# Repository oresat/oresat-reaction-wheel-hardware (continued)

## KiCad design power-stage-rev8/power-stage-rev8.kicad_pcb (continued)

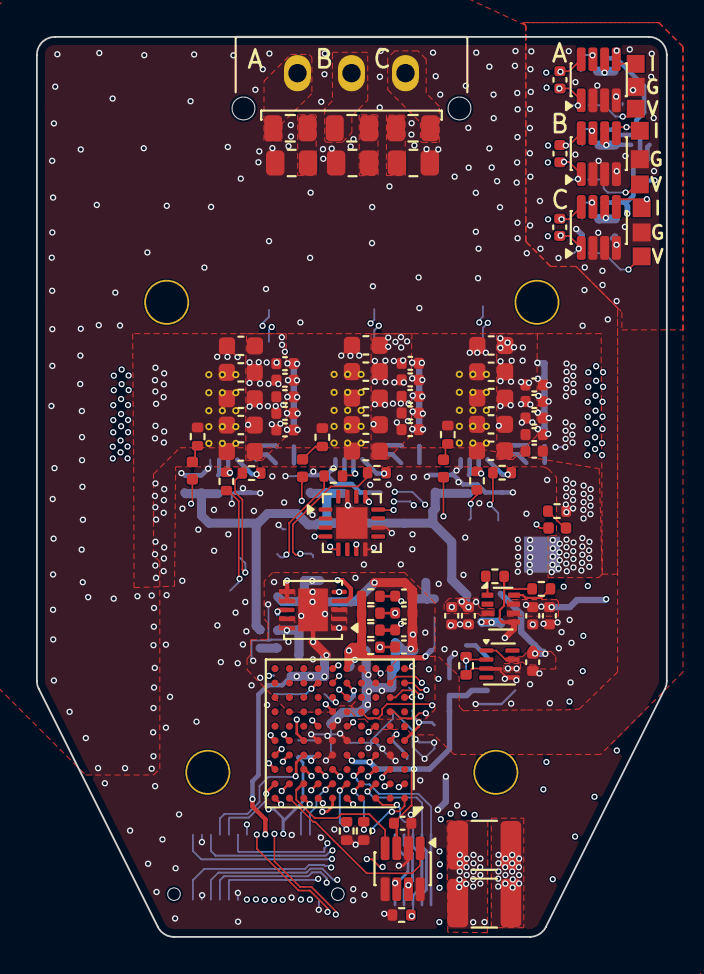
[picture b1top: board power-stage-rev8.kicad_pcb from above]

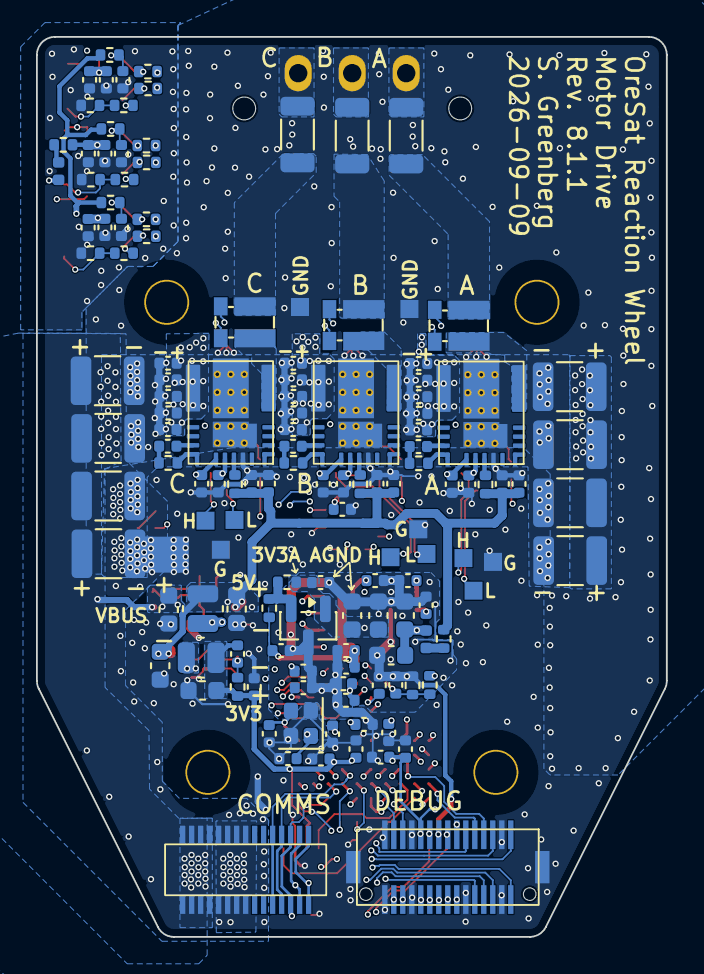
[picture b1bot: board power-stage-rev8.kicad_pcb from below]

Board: 6 copper layers, 35.0 x 50.0 mm, 235 parts (138 on the bottom side), 122 nets.

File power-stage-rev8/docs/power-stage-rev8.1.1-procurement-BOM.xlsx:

Reference | Qty | Value | DNP | Exclude from BOM | Footprint | Mfg | MPN | Order qty | Src | Ordered | Note
C2,C27,C96,C97,C98,C99,C100,C101,C106,C107 | 10 | 47u |  |  | Capacitor_SMD:C_1210_3225Metric | Murata | GRT32EC81C476KE13L | 110 | Digi
C3,C9,C13,C14,C16,C17,C18,C33,C39,C41,C49,C50,C55,C57,C65,C66,C71,C73,C81,C82,C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 | 21 | 100n |  |  | Capacitor_SMD:C_0402_1005Metric | Murata | GRT155R71E104KE01J | 231 | Digi
C4,C15,C21,C23,C24,C46,C48,C62,C64,C78,C80,C90,C91,C92,C109,C110,C112,C113,C115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 | 20 | 10u |  |  | Capacitor_SMD:C_0603_1608Metric | Murata | GRT188C81C106ME13D | 220 | LCSC
C5,C42,C43,C44,C45,C58,C59,C60,C61,C74,C75,C76,C77,C86,C93,C94,C95,C117,C118,C1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 | 32 | 2.2u |  |  | Capacitor_SMD:C_0402_1005Metric | Murata | GRT155C81C225ME13D | 352 | LCSC |  | Alt: GRM155C81C225KE11D
C7,C20,C25,C26,C28 | 5 | 1u |  |  | Capacitor_SMD:C_0402_1005Metric | Murata | GRT155C81A105ME01D | 55 | Digi
C8,C10 | 2 | 18p |  |  | Capacitor_SMD:C_0402_1005Metric | Murata | GCM1555C1H180JA16D | 22 | Digi
C11,C12,C35,C36,C37,C51,C53,C67,C69,C83,C87,C88,C89,C102,C103,C104,C105 | 17 | 4.7u |  |  | Capacitor_SMD:C_0402_1005Metric | Murata | GRT155C81A475ME13J | 187 | Digi |  | Alt: GRM155D81A475ME15D
C19 | 1 | 10n |  |  | Capacitor_SMD:C_0402_1005Metric | Murata | GCM155R71H103KA55D | 11 | Digi
C22,C29,C30 | 3 | 22u |  |  | Capacitor_SMD:C_0603_1608Metric | Murata | GRT188C80J226ME13D | 33 | Digi |  | Alt: KGM15CS60J226MT
C31,C32,C34 | 3 | 3.3n |  |  | Capacitor_SMD:C_0805_2012Metric | Murata | GCM2165C2A332JA16D | 33 | Digi
C38,C40,C54,C56,C70,C72 | 6 | 47p |  |  | Capacitor_SMD:C_0402_1005Metric | Murata | GCM1555C1H470JA16D | 66 | Digi
C108 | 1 | 120p |  |  | Capacitor_SMD:C_0402_1005Metric | Murata | GRM1555C1H121JA01D | 11 | Digi
FB1,FB5,FB6,FB7,FB9 | 5 | BLM15PX601SZ1 |  |  | Inductor_SMD:L_0402_1005Metric | Murata | BLM15PX601SZ1D | 55 | Digi
FB2,FB3,FB4 | 3 | BLM31SN500SN1L |  |  | Inductor_SMD:L_1206_3216Metric | Murata | BLM31SN500SN1L | 33 | Digi
FB8 | 1 | 0 |  |  | Inductor_SMD:L_0402_1005Metric | Yageo | AC0402FR-070RL | 11 | Digi
J1 | 1 | MEZZ |  |  | rev-8-footprints:0555600307 | Molex | 555600307 | 11 | Digi
J3 | 1 | 10132797-031100LF |  |  | rev-8-footprints:10132797-031100LF_1 | Amphenol | 10132797-031100LF | 11 | Digi
L1 | 1 | 1u |  |  | rev-8-footprints:L_Murata_DFE201612E_2016Metric | Murata | DFE201612E-1R0M=P2 | 11 | Digi
L2 | 1 | 2.2u |  |  | rev-8-footprints:L_Murata_DFE201612E_2016Metric | Murata | DFE201612E-2R2M=P2 | 11 | Digi
R1,R21,R32,R43 | 4 | 8.2k/0.1% |  |  | Resistor_SMD:R_0402_1005Metric | Yageo | RP0402BRD078K2L | 44 | LCSC |  | Alt: TNPW04028K20BEED
R2,R22,R33,R44 | 4 | 2.7k/0.1% |  |  | Resistor_SMD:R_0402_1005Metric | Yageo | RP0402BRD072K7L | 44 | Digi |  | Alt: TNPW04022K70BEED
R5,R20,R42,R45,R46 | 5 | 3.3k |  |  | Resistor_SMD:R_0402_1005Metric | Yageo | AC0402FR-073K3L | 55 | Digi
R6 | 1 | 470m |  |  | Resistor_SMD:R_0402_1005Metric | Yageo | PE0402FRF7W0R47L | 11 | Digi
R7,R8,R9 | 3 | 12 |  |  | Resistor_SMD:R_0805_2012Metric | Yageo | SR0805FR-7T12RL | 33 | Digi
R11 | 1 | 100m |  |  | Resistor_SMD:R_0402_1005Metric | Yageo | PE0402FRF470R1L | 11 | Digi
R12,R13,R23,R24,R34,R35 | 6 | 22 |  |  | Resistor_SMD:R_0402_1005Metric | Yageo | AC0402FR-0722RL | 66 | Digi
R14,R15,R25,R26,R36,R37 | 6 | 2.7 |  |  | Resistor_SMD:R_0402_1005Metric | Yageo | AC0402FR-072R7L | 66 | Digi
R16,R18,R19,R27,R29,R30,R31,R38,R40,R41 | 10 | 0 |  |  | Resistor_SMD:R_0402_1005Metric | Yageo | AC0402FR-070RL | 110 | Digi
R17,R28,R39 | 3 | 2m |  |  | Resistor_SMD:R_Shunt_Vishay_WSKW0612 | Vishay | WSKW06122L000FEA | 33 | LCSC | TODO order
R49 | 1 | 453k |  |  | Resistor_SMD:R_0402_1005Metric | Yageo | AC0402FR-07453KL | 11 | Digi
R50 | 1 | 100k |  |  | Resistor_SMD:R_0402_1005Metric | Yageo | AC0402FR-07100KL | 11 | Digi
R51 | 1 | 34k |  |  | Resistor_SMD:R_0402_1005Metric | Yageo | AC0402FR-0734KL | 11 | Digi
R52 | 1 | 80.6k |  |  | Resistor_SMD:R_0402_1005Metric | Yageo | AC0402FR-0780K6L | 11 | Digi
TH1,TH2,TH3,TH4 | 4 | Thermistor_NTC_US |  |  | Resistor_SMD:R_0402_1005Metric | Murata | NCU15XH103F6SRC | 44 | Digi
U1 | 1 | TCAN330 |  |  | Package_TO_SOT_SMD:SOT-23-8 | TI | TCAN330DCNR | 11 | Digi
U3 | 1 | STM32G474VEHx |  |  | Package_BGA:TFBGA-100_8x8mm_Layout10x10_P0.8mm | ST | STM32G474VEH3 | 11 | Digi |  | Alt: STM32G474VEH6
U4 | 1 | TPS629210 |  |  | Package_TO_SOT_SMD:SOT-583-8 | TI | TPS629210DRLR | 11 | Digi
U5 | 1 | ADP7156ACPZ |  |  | Package_DFN_QFN:DFN-10-1EP_3x3mm_P0.5mm_EP1.65x2.38mm | AD | ADP7156ACPZ-3.3-R7 | 11 | Digi
U6 | 1 | MA732 |  |  | Package_DFN_QFN:QFN-16-1EP_3x3mm_P0.5mm_EP1.75x1.75mm | MPS | MA732GQ-Z | 11 | Digi
U7 | 1 | REF3030E |  |  | Package_TO_SOT_SMD:SOT-23 | TI | REF3030AIDBZR | 11 | Digi
U8,U10,U12 | 3 | LMG2100R044 |  |  | rev-8-footprints:TI_torment_nexus | TI | LMG2100R044RARR | 33 | Digi
U9,U11,U13 | 3 | INA296A3 |  |  | Package_TO_SOT_SMD:SOT-23-8 | TI | INA296A3QDDFRQ1 | 33 | Digi
U14 | 1 | TPS62821DLC |  |  | Package_SON:Texas_VSON-HR-8_1.5x2mm_P0.5mm | TI | TPS62821DLCR | 11 | Digi
Y1 | 1 | Crystal_GND24 |  |  | Crystal:Crystal_SMD_2016-4Pin_2.0x1.6mm | IQD | LFXTAL071255 | 11 | Digi |  | Alt: LFXTAL082887

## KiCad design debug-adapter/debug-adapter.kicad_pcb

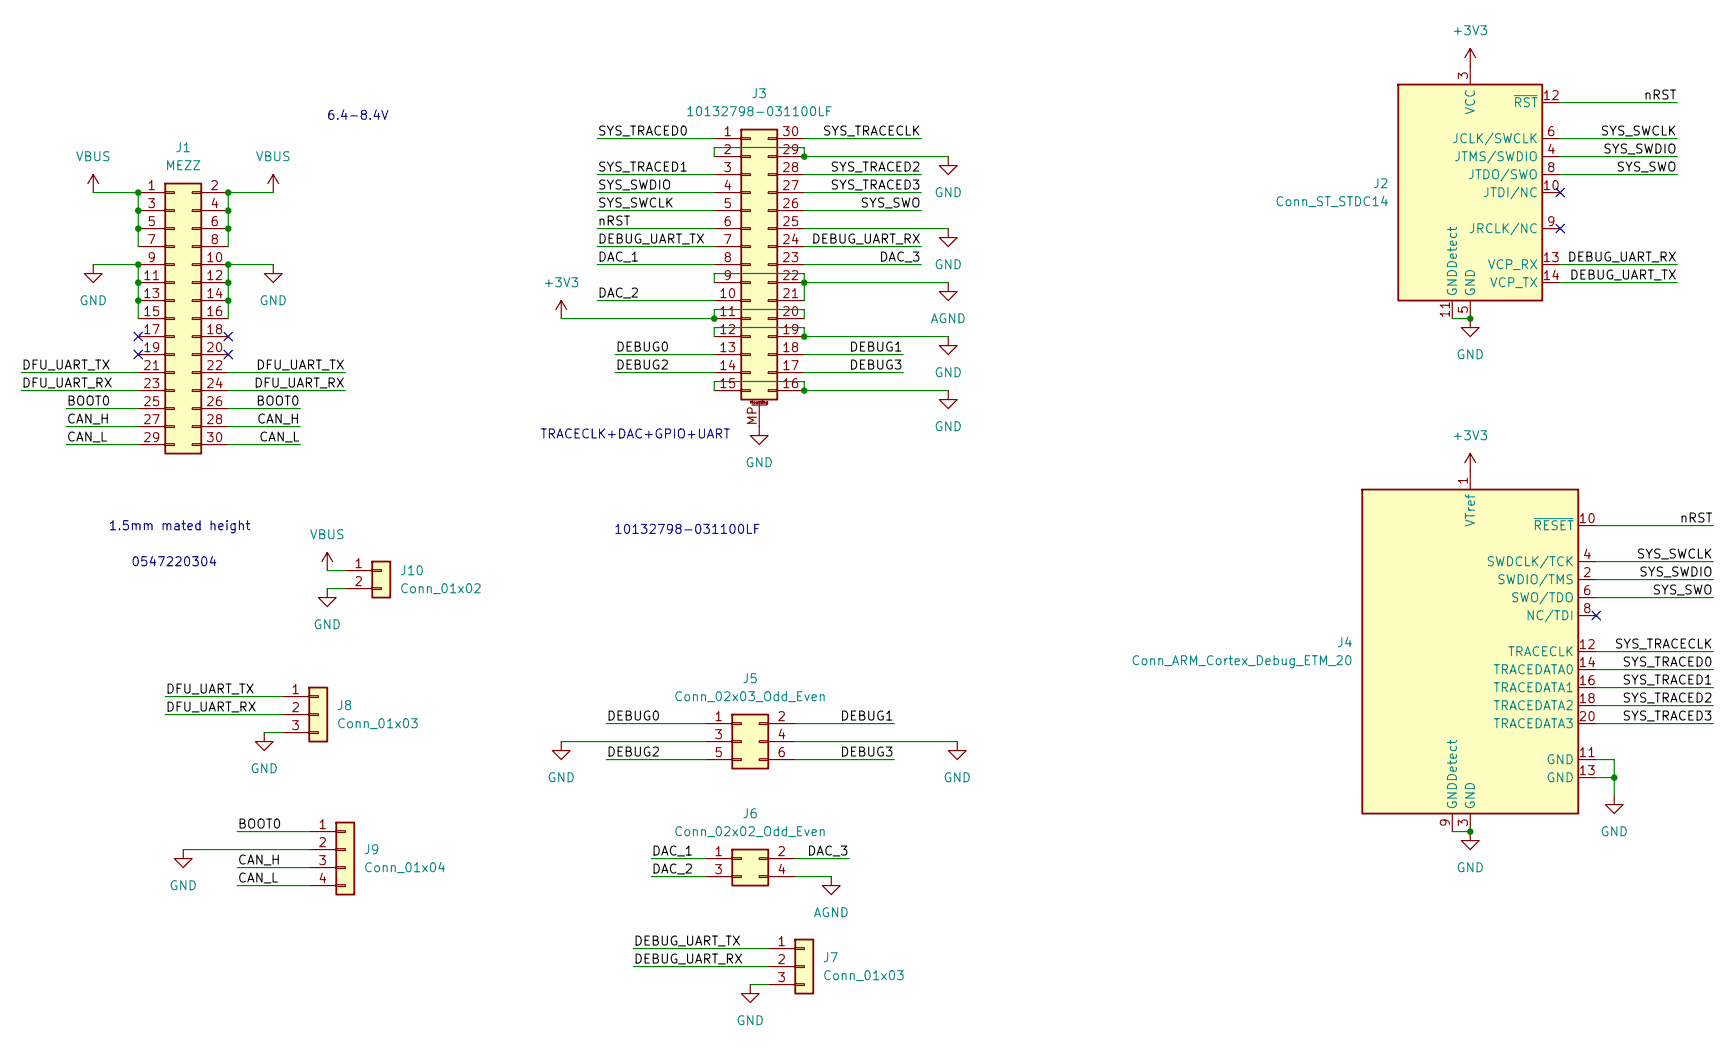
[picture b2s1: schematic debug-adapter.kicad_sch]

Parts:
J1: MEZZ; 0547220304; MPN 0547220304
J2: Conn_ST_STDC14; PinHeader_2x07_P1.27mm_Vertical_SMD
J3: 10132798-031100LF; MPN 10132798-031100LF
J4: Conn_ARM_Cortex_Debug_ETM_20; PinHeader_2x10_P1.27mm_Vertical_SMD
J5: Conn_02x03_Odd_Even; PinHeader_2x03_P2.54mm_Vertical_SMD
J6: Conn_02x02_Odd_Even; PinHeader_2x02_P2.54mm_Vertical_SMD
J7, J8: Conn_01x03; PinHeader_1x03_P2.54mm_Vertical_SMD_Pin1Left
J9: Conn_01x04; PinHeader_1x04_P2.54mm_Vertical_SMD_Pin1Left
J10: Conn_01x02; PinHeader_1x02_P2.54mm_Vertical_SMD_Pin1Left

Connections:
+3V3: J2.3 (VCC), J3.11, J3.20, J4.1 (VTref)
/BOOT0: J1.25, J1.26, J9.1
/CAN_H: J1.27, J1.28, J9.3
/CAN_L: J1.29, J1.30, J9.4
/DAC_1: J3.8, J6.1
/DAC_2: J3.10, J6.3
/DAC_3: J3.23, J6.2
/DEBUG0: J3.13, J5.1
/DEBUG1: J3.18, J5.2
/DEBUG2: J3.14, J5.5
/DEBUG3: J3.17, J5.6
/DEBUG_UART_RX: J2.13 (VCP_RX), J3.24, J7.2
/DEBUG_UART_TX: J2.14 (VCP_TX), J3.7, J7.1
/DFU_UART_RX: J1.23, J1.24, J8.2
/DFU_UART_TX: J1.21, J1.22, J8.1
/SYS_SWCLK: J2.6 (JCLK/SWCLK), J3.5, J4.4 (SWDCLK/TCK)
/SYS_SWDIO: J2.4 (JTMS/SWDIO), J3.4, J4.2 (SWDIO/TMS)
/SYS_SWO: J2.8 (JTDO/SWO), J3.26, J4.6 (SWO/TDO)
/SYS_TRACECLK: J3.30, J4.12 (TRACECLK)
/SYS_TRACED0: J3.1, J4.14 (TRACEDATA0)
/SYS_TRACED1: J3.3, J4.16 (TRACEDATA1)
/SYS_TRACED2: J3.28, J4.18 (TRACEDATA2)
/SYS_TRACED3: J3.27, J4.20 (TRACEDATA3)
/nRST: J2.12 (~RST), J3.6, J4.10 (~RESET)
AGND: J3.9, J3.21, J3.22, J6.4
GND: J1.9, J1.10, J1.11, J1.12, J1.13, J1.14, J1.15, J1.16, J2.5 (GND), J2.7 (GND), J2.11 (GNDDetect), J3.2, J3.12, J3.15, J3.16, J3.19, J3.25, J3.29, J3.MP (MountPin), J4.3 (GND), J4.5 (GND), J4.9 (GNDDetect), J4.11 (GND), J4.13 (GND), J4.15 (GND), J4.17 (GND), J4.19 (GND), J5.3, J5.4, J7.3, J8.3, J9.2, J10.2
VBUS: J1.1, J1.2, J1.3, J1.4, J1.5, J1.6, J1.7, J1.8, J10.1

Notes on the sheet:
6.4-8.4V
TRACECLK+DAC+GPIO+UART
1.5mm mated height
0547220304
10132798-031100LF

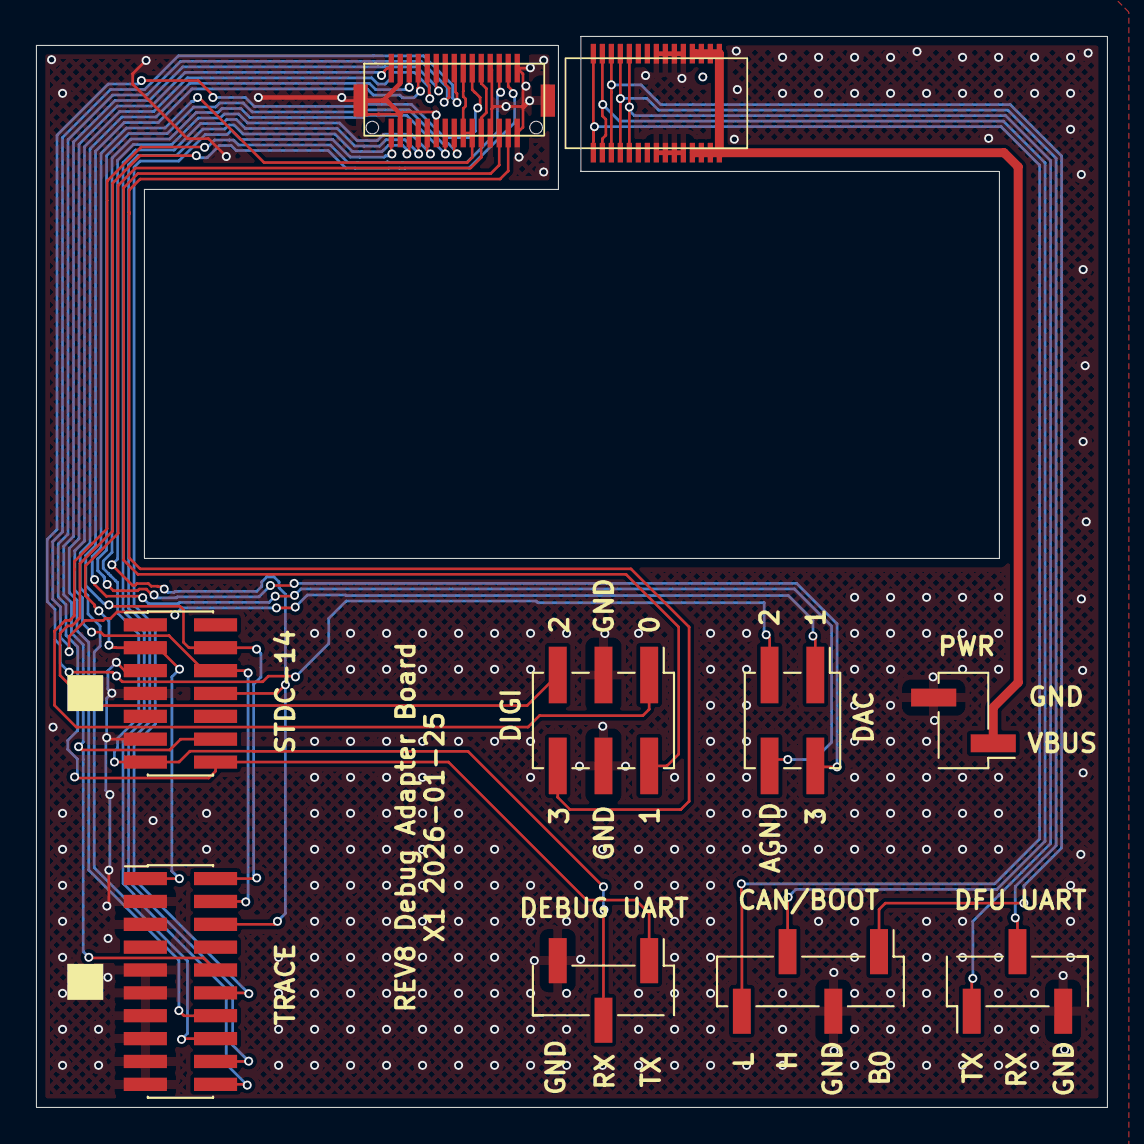
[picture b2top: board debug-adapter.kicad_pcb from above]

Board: 2 copper layers, 59.5 x 59.5 mm, 10 parts (0 on the bottom side), 27 nets.

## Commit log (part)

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2026-01-02 Layout close to done
2026-01-02 Add fill under bulk caps next to power connector
2026-01-05 RC1 - clean up zones, add test points, silkscreen, stitching vias
2026-01-05 RC2 - Add STEP file, clean up AGND zone borders, make shunt sense lines cross plane gaps at right angles
2026-03-24 Add debug adapter
2026-05-07 Kicad v10 update
